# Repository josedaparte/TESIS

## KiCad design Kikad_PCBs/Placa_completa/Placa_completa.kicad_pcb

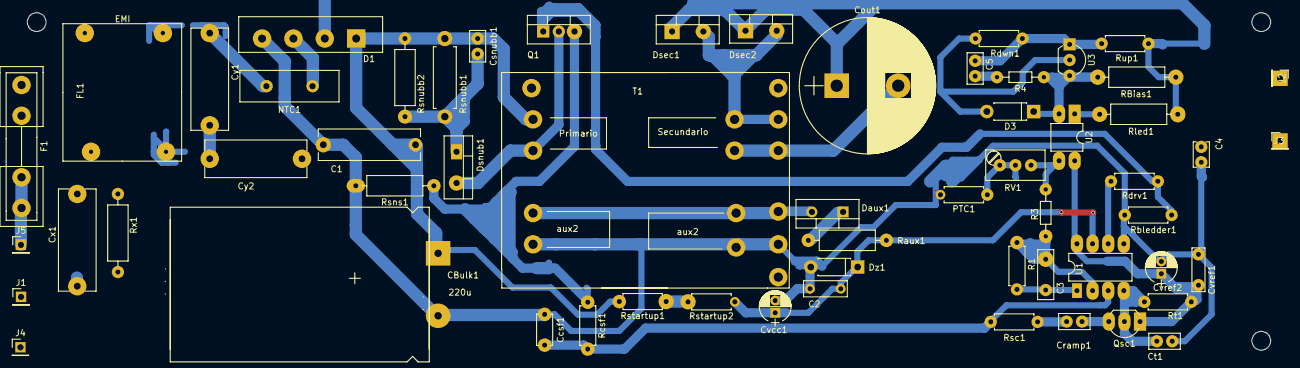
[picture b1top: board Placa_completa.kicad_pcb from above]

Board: 2 copper layers, 202.2 x 54.9 mm, 59 parts (0 on the bottom side), 34 nets.

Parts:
C1: 0.1u; C_Rect_L16.5mm_W5.0mm_P15.00mm_MKT
C2: 100n; C_Rect_L7.0mm_W2.5mm_P5.00mm
C3: 10n; C_Disc_D8.0mm_W2.5mm_P5.00mm
C4: 10n; C_Rect_L4.0mm_W2.5mm_P2.50mm
C5: 1.5n; C_Disc_D5.0mm_W2.5mm_P2.50mm
CBulk1: 220u; CP_Axial_L42.0mm_D23.0mm_P45.00mm_Horizontal
Ccsf1: 100p; C_Disc_D5.0mm_W2.5mm_P5.00mm
Cout1: 330u; CP_Radial_D22.0mm_P10.00mm_SnapIn
Cramp1: 10n; C_Disc_D5.0mm_W2.5mm_P2.50mm
Csnubb1: 39p; C_Disc_D5.0mm_W2.5mm_P2.50mm
Ct1: 1n; C_Disc_D5.0mm_W2.5mm_P2.50mm
Cvcc1: 22u; CP_Radial_D5.0mm_P2.00mm
Cvref1: 100n; C_Rect_L7.0mm_W2.0mm_P5.00mm
Cvref2: 10u; CP_Radial_D5.0mm_P2.00mm
Cx1: 100n; C_Rect_L16.5mm_W6.0mm_P15.00mm_MKT
Cy1, Cy2: 100n; C_Rect_L16.5mm_W6.0mm_P15.00mm_MKT
D1: D_Bridge_-A+A; Diode_Bridge_18.5x5.5
D3: 10V; D_DO-41_SOD81_P7.62mm_Horizontal
Daux1: N1106; TO-220-2_Vertical
Dsec1, Dsec2: BYV29X; TO-220-2_Vertical
Dsnub1: D; TO-220-2_Vertical
Dz1: 20V; D_DO-41_SOD81_P7.62mm_Horizontal
F1: Fuse_Small; Fuseholder5x20_horiz_open_inline_Type-I
FL1: EMI; choke_tesis
J1: N; Pin_Header_Straight_1x01_Pitch2.54mm
J2: Vo+; Pin_Header_Straight_1x01_Pitch2.54mm
J3: VoGnd; Pin_Header_Straight_1x01_Pitch2.54mm
J4: Earth; Pin_Header_Straight_1x01_Pitch2.54mm
J5: L; Pin_Header_Straight_1x01_Pitch2.54mm
NTC1: I5D20R; C_Disc_D16.0mm_W5.0mm_P7.50mm
PTC1: PTC; R_Axial_DIN0207_L6.3mm_D2.5mm_P7.62mm_Horizontal
Q1: FQP8N60C; TO-220-3_Vertical
Qsc1: BC548; TO-92_Inline_Wide
R1: 10k; R_Axial_DIN0207_L6.3mm_D2.5mm_P7.62mm_Horizontal
R3, R4: 4k7; R_Axial_DIN0204_L3.6mm_D1.6mm_P7.62mm_Horizontal
RBias1: 8k2; R_Axial_DIN0309_L9.0mm_D3.2mm_P12.70mm_Horizontal
RV1: 1k; Potentiometer_Trimmer_Bourns_3296W
Raux1: 1k; R_Axial_DIN0309_L9.0mm_D3.2mm_P12.70mm_Horizontal
Rbledder1: 22k; R_Axial_DIN0207_L6.3mm_D2.5mm_P7.62mm_Horizontal
Rcsf1: 3k9; R_Axial_DIN0207_L6.3mm_D2.5mm_P7.62mm_Horizontal
Rdrv1: 10; R_Axial_DIN0207_L6.3mm_D2.5mm_P7.62mm_Horizontal
Rdwn1: 3k9; R_Axial_DIN0207_L6.3mm_D2.5mm_P7.62mm_Horizontal
Rled1: 8k2; R_Axial_DIN0309_L9.0mm_D3.2mm_P12.70mm_Horizontal
Rsc1: 22k; R_Axial_DIN0207_L6.3mm_D2.5mm_P7.62mm_Horizontal
Rsns1: 0.33; R_Axial_DIN0309_L9.0mm_D3.2mm_P12.70mm_Horizontal
Rsnubb1: 6k8; R_Axial_DIN0411_L9.9mm_D3.6mm_P12.70mm_Horizontal
Rsnubb2: 6k8; R_Axial_DIN0309_L9.0mm_D3.2mm_P12.70mm_Horizontal
Rstartup1, Rstartup2: 82K; R_Axial_DIN0207_L6.3mm_D2.5mm_P7.62mm_Horizontal
Rt1: 15k; R_Axial_DIN0207_L6.3mm_D2.5mm_P7.62mm_Horizontal
Rup1: 82k; R_Axial_DIN0207_L6.3mm_D2.5mm_P7.62mm_Horizontal
Rx1: 180k; R_Axial_DIN0309_L9.0mm_D3.2mm_P12.70mm_Horizontal
T1: Transformer_1P_2S; Trafo_CHK-EI30-2VA_1xSec
U1: UC2844N; DIP-8_W7.62mm_LongPads
U2: PC817; DIP-4_W7.62mm_LongPads
U3: TL431; TO-92_Inline_Wide

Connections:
/Etapa de control/Gate: Q1.1, Rbledder1.2, Rdrv1.1
/Etapa de control/Isense: Q1.3, Rcsf1.1, Rsns1.1
/Etapa de control/Vaux: C2.1, Cvcc1.1, Dz1.1, Raux1.1, Rstartup2.1, U1.7
Earth: C1.2, C2.2, C4.1, CBulk1.2, Ccsf1.1, Ct1.1, Cvcc1.2, Cvref1.1, Cvref2.2, D1.1, Dz1.2, PTC1.2, Rbledder1.1, Rsns1.2, T1.6, U1.5
Earth_Protective: Cy1.2, Cy2.1, J4.1
GND: C4.2, Cout1.2, D3.2, J3.1, Rdwn1.1, T1.4, U3.2
GNDPWR: Cx1.2, FL1.3, J1.1, Rx1.1
unnamed: C1.1, CBulk1.1, Csnubb1.1, D1.3, Rsnubb1.2, Rsnubb2.2, Rstartup1.2, T1.1
unnamed: C3.1, R1.1, U1.1
unnamed: C3.2, R1.2, R3.1, U1.2
unnamed: C5.1, Rdwn1.2, Rup1.1, U3.1
unnamed: C5.2, R4.2
unnamed: Ccsf1.2, Rcsf1.2, Rsc1.2, U1.3
unnamed: Cramp1.1, Rsc1.1
unnamed: Cramp1.2, Qsc1.3
unnamed: Csnubb1.2, Dsnub1.1, Rsnubb1.1, Rsnubb2.1
unnamed: Ct1.2, Qsc1.2, Rt1.2, U1.4
unnamed: Cvref1.2, Cvref2.1, Qsc1.1, Rt1.1, U1.8, U2.4
unnamed: Cx1.1, F1.2, FL1.1, Rx1.2
unnamed: Cy1.1, FL1.2, NTC1.2
unnamed: Cy2.2, D1.2, FL1.4
unnamed: D1.4, NTC1.1
unnamed: D3.1, R4.1, RBias1.1, U2.2, U3.3
unnamed: Daux1.1, Raux1.2
unnamed: Daux1.2, T1.5
unnamed: Dsec1.2, Dsec2.2, T1.3
unnamed: Dsnub1.2, Q1.2, T1.2
unnamed: PTC1.1, RV1.1, RV1.2
unnamed: R3.2, RV1.3, U2.3
unnamed: Rdrv1.2, U1.6
unnamed: Rled1.1, U2.1
unnamed: Rstartup1.1, Rstartup2.2
VAC: F1.1, J5.1
VD: Cout1.1, Dsec1.1, Dsec2.1, J2.1, RBias1.2, Rled1.2, Rup1.2

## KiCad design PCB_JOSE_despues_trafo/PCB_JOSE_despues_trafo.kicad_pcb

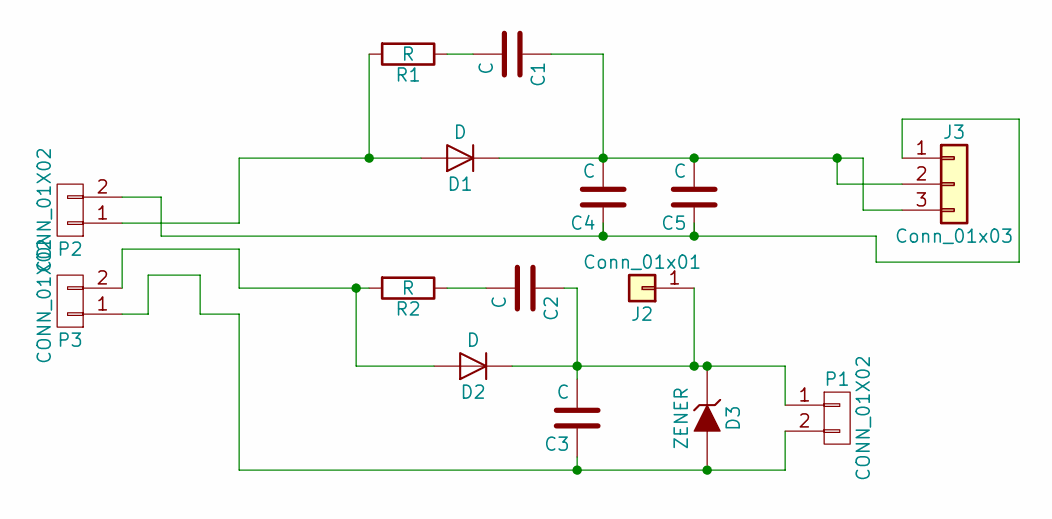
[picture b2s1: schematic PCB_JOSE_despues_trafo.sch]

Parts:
C1, C2, C3, C4, C5: C; CP_Radial_D6.3mm_P2.50mm
D1, D2: D; D_DO-41_SOD81_P10.16mm_Horizontal
D3: ZENER; D_DO-41_SOD81_P10.16mm_Horizontal
J2: Conn_01x01; PINTST
J3: Conn_01x03; bornier3
P1, P2, P3: CONN_01X02; bornier2
R1, R2: R; R_Axial_DIN0207_L6.3mm_D2.5mm_P10.16mm_Horizontal

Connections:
unnamed: C1.1, C4.2, C5.2, D1.1 (K), J3.2, J3.3
unnamed: C1.2, R1.1
unnamed: C2.1, C3.2, D2.1 (K), D3.1 (K), J2.1, P1.1
unnamed: C2.2, R2.1
unnamed: C3.1, D3.2 (A), P1.2, P3.1
unnamed: C4.1, C5.1, J3.1, P2.2
unnamed: D1.2 (A), P2.1, R1.2
unnamed: D2.2 (A), P3.2, R2.2

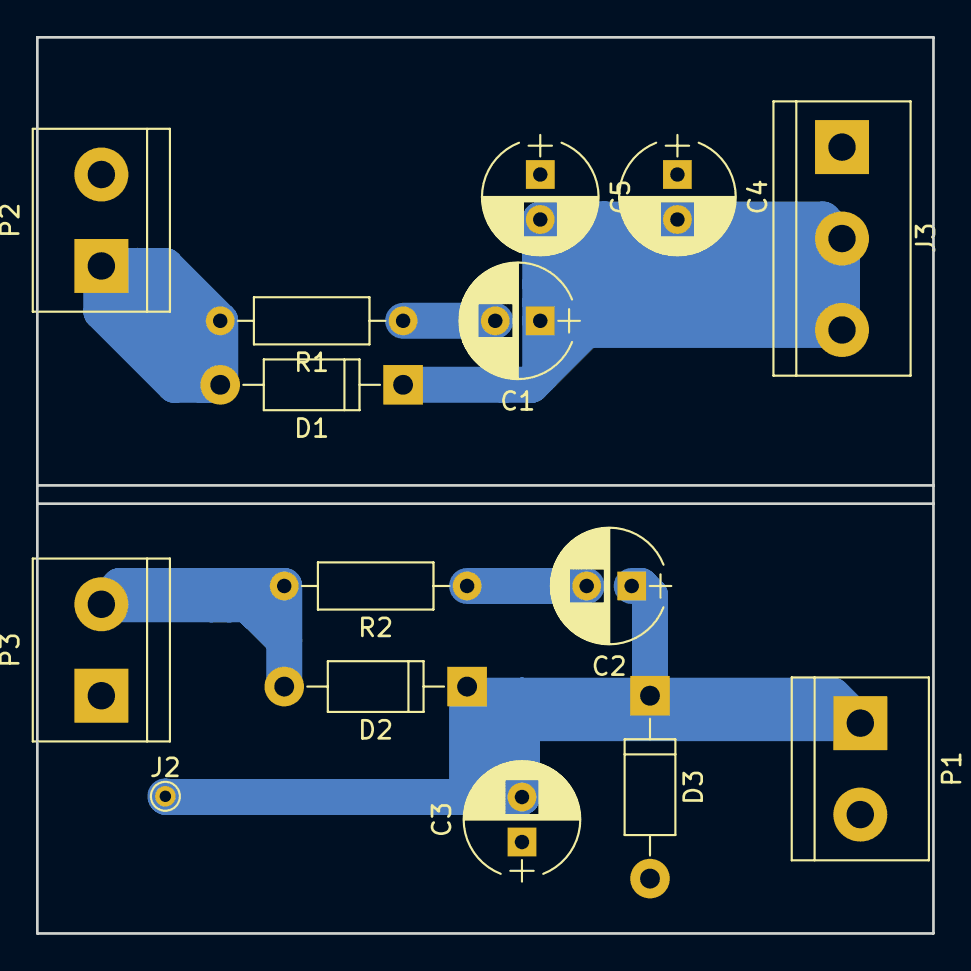
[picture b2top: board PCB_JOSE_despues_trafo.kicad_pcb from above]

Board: 2 copper layers, 49.8 x 49.8 mm, 15 parts (0 on the bottom side), 8 nets.

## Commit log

2018-04-30 Agrego los proyectos de KiCAD del mosfet ultimo implementado y del circuito posterior al transformador
2018-05-04 Creacion carpeta datasheets, paginas y documentos utiles
    doc y pag utiles son ejemplos de uso de integrados, esxplicaciones de circuitos y de funcionamiento de cosas que pueden ser de utilidad
2018-05-08 Comienzo diseño PWM propio
    creo la carpeta Diseño_PWM, para poner todo lo referido a este, y tambien el documento de lyx que sera un tipomanual donde esta todo el diseño paso a paso y las explicaciones de todo
2018-05-22 continuación informe pwm y agrego simulacion de fuente de corriente
    en la carpeta simulaciones agrego la simulacion de la fuente flyback con el control nuevo para que sea fuente de corriente, esta regula a 2.1A independientemente de la carga.
    si al cambiar la carga regula a menos corriente de para la que esta diseñada es porque se la esta limitando desde la pata isense del primario (maxima corriente del primario), para no romper todo por 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
    agregado de cosas al informe de diseño del pwm.
    agregado de datasheets y pdfs utiles
2018-10-11 Calculo Fuente Matlab, docuumentos importantes y simulaciones.
    Documentos nuevos: identificar trafo saturado
    uc3842 explicacion español
    diseño de fuente flyback paso a paso por texas instruments
    Creacion de scripts de MATLAB, son 2 uno siguiendo el diseño de texas y uno propio, donde al correrlo se calcula paso por paso cada componente del circuito. llegue hasta 9.2.2.8
2018-10-11 Correccion, el documento agregado anteriormente era otro, lo agrego y digo cual era el anterior
    El anterior es el diseño completo hecho por la pagina de texas de una fuente 120V y 1A, como para guiarse con el diseño en matlab, ahora agrego el datasheet del uc384x con el calculo y explicacion pa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
    (detalle falta el calculo del nucleo)
2018-10-17 Continuacion calculos fuente guiando con PDF de texas y publico PDF con los resultados
    llega hasta la respuesta en frecuencia de la etapa de potencia. ahora seguiria la realimentacion.
    el PDF publicado no llega hasta lo de matlab, es de la version anterior de los scripts
2018-10-18 Modificacion de scripts poco significativas
    modificacion parametros de diseño, salidas de texto y optimizacion del script
2018-10-18 Agrego documento del calculo completo pero revision mas nueva y calculo fuente de script que usariamos
    agrego el pdf del scrip con la fuente que usariamos 100v 1.2A, mas un calculo del simulador de texas con los mismos valores para comparacion.
    el pdf del datasheet es la nueva revision, tiene corregido el tema de lm y lp pero los calculos son distintos creo, hbria que leerlo bien
2018-10-19 Agrego libros, datasheets de MOSFET, paginas utiles y modificacion del calculo fuente con posifle mosfet a utilizar
    Agrego datasheets de mosfet posibles de utilizar, libro para ver calculo de transformador.
    calculo los componentes de la fuente nuevamente con el posible mosfet para usar (fqp5n60c)
    orden de archivos
2018-10-19 borro simulaciones inncecesarias
2018-10-25 Actualizacion scripts y txt con la seleccion de componentes. simulacion parte tl y opto
2018-10-25 Proyecto KiCad para el PCB del PWM igual que el datasheet revision E
    Esquematico completo, falta asociar las huellas
2018-10-29 PCB del pwm terminado
2018-11-01 modificacion de serigrafia del PCB y pdf serigrafi
2018-11-01 Calculos 80v 1.5A
2018-11-02 Completo todo el script calculo fuente del PDF
    me falta que me de igual la funcion de transferencia de lazo abierto
2018-11-02 Terminados los scripts, bodes dan igual que dtsht
    todos los calculos terminados del datasheet, los bodes dan exactamente
    iguales que en el datasheet uc3842 rev E.
2018-11-02 Creacion BOM y finalizacion diseño fuente nuestra
2018-11-16 ultimo PCB con las serigrafias V2 (el qeu implemente y funcionaba)
2018-11-20 pcb con esquematico y valores
2018-12-17 Diselo placa final en kicad 65v 1.5A
2019-02-01 Placa final diseño completo.
    Diseño kicad de la placa funcionando, falta hacer las modificaciones para que quede listo como para mandar a hacer, tambien modificar los conectores de entrada (Vac) y salida a la carga para que qued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
2019-02-01 Gant para presentar el 8/12 y modificaciones al PCB
2019-02-01 modificaciones al pcb
2019-02-04 cambio proyecto kicad por el que usamos en la primer fuente completa y modificacion de tamaños, bordes rellenos adaptado a la placa final. Falta ver que queden bien las serigrafias y modificar los co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
2019-02-04 Placa completa terminada por jose, falta revision de los chicos
    corregidas las serigrafias, estan todas en la capa top y las pistas. hay que revisar de nuevo los tamaños para que entre bien en la carcasa, averiguar com es lo de los huecos y si tiene que tener mar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
2019-10-25 Placa tesis finalizada y montada y funcionando
